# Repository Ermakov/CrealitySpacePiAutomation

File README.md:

# Creality SpacePi automation and control module
This is PCB and Arduino IDE sketch for Creality Space Pi (Plus or not) automation.

Description:
- necessary the module itself and IDC10 female-male cable
- can be inserted into any Creality SpacePi dryer (double, single, built-in Creality CFS or not)
- other functions and cables are optional (backlights, external control and power are not required for operation, but can be connected additionally)
- the cable from the SpacePi display needs to be disconnected from the dryer board and inserted into the "display" socket on the module
- an additional IDC10 cable connecting between the module "mainboard" socket and the dryer board (power is supplied from the dryer board via this cable)
- RJ45 on the module connecting to any I2C master using a regular patch cord and provides data transfer in both directions, and also serves lighting (24V led strip) inside CFS or dryer
- two pin terminal block on the module used for connecting the led strip; pad J4 on the back of the module (via diode) used for supply 24 volts to the strip directly from CFS (without connecting a patch cord with external power)

Module/sketch features:
- interception of all signals between the display/buttons and the dryer board, the module sees the readings on the display and can control the dryer buttons
- automatic switching on SpacePi after power is supplied
- automatic switching on SpacePi drying mode to the values on the display when the module sees humidity above the set point (by default 30%, switching on for 4 hours, then a break of 4 hours, and so on)
- solving the problem with the E4 error (when the dryer does not reach the expected temperature within 10 minutes) by restarting the drying mode every 9 minutes (until heating to the working temperature)
- transferring data of temperature/humidity in the dryer via I2C as HTU21D sensor protocol
- any information from the dryer display (including an error), as well as pressing any buttons using special I2C commands (see the sketch)

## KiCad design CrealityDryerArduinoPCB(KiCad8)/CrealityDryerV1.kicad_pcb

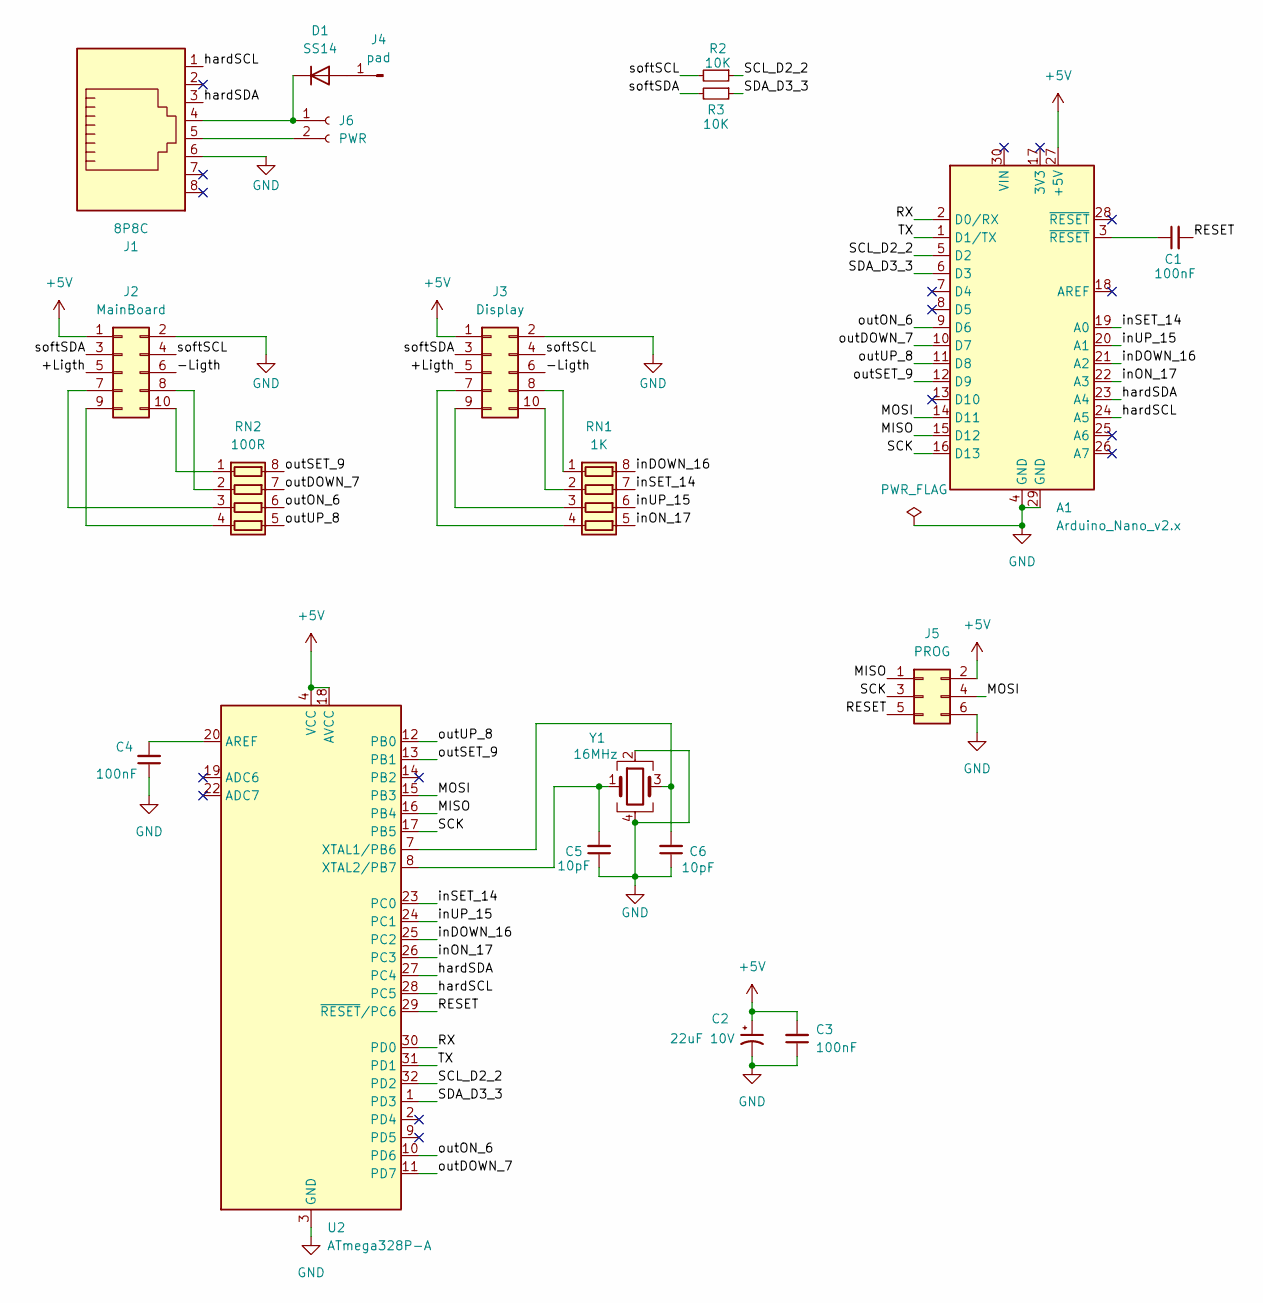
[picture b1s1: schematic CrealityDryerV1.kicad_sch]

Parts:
A1: Arduino_Nano_v2.x; Arduino_Nano
C1, C3, C4: 100nF; C_0603_1608Metric
C2: 22uF 10V; CP_EIA-3528-12_Kemet-T
C5, C6: 10pF; C_0603_1608Metric
D1: SS14; D_SMA
J1: 8P8C; RJ45_OST_PJ012-8P8CX_VerticalSensor
J2: MainBoard; IDC-Famale_2x05_P2.54mm_VerticalSilk
J3: Display; IDC-Header_2x05_P2.54mm_VerticalSilk
J4: pad; TestPoint_Pad_1.5x1.5mm
J5: PROG; PinHeader_2x03_P2.54mm_Vertical
J6: PWR; DG141R-2.54-02P
R2, R3: 10K; R_0603_1608Metric
RN1: 1K; R_Array_Convex_4x0603
RN2: 100R; R_Array_Convex_4x0603
U2: ATmega328P-A; TQFP-32_7x7mm_P0.8mm
Y1: 16MHz; Crystal_SMD_3225-4Pin_3.2x2.5mm

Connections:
+5V: A1.27 (+5V), C2.1, C3.2, J2.1, J3.1, J5.2, U2.4 (VCC), U2.6 (VCC), U2.18 (AVCC)
/+Ligth: J2.5, J3.5
/-Ligth: J2.6, J3.6
/MISO: A1.15 (D12), J5.1, U2.16 (PB4)
/MOSI: A1.14 (D11), J5.4, U2.15 (PB3)
/RESET: C1.2, J5.5, U2.29 (~RESET/PC6)
/RX: A1.2 (D0/RX), U2.30 (PD0)
/SCK: A1.16 (D13), J5.3, U2.17 (PB5)
/SCL_D2_2: A1.5 (D2), R2.1, U2.32 (PD2)
/SDA_D3_3: A1.6 (D3), R3.1, U2.1 (PD3)
/TX: A1.1 (D1/TX), U2.31 (PD1)
/hardSCL: A1.24 (A5), J1.1, U2.28 (PC5)
/hardSDA: A1.23 (A4), J1.3, U2.27 (PC4)
/inDOWN_16: A1.21 (A2), RN1.8 (R1.2), U2.25 (PC2)
/inON_17: A1.22 (A3), RN1.5 (R4.2), U2.26 (PC3)
/inSET_14: A1.19 (A0), RN1.7 (R2.2), U2.23 (PC0)
/inUP_15: A1.20 (A1), RN1.6 (R3.2), U2.24 (PC1)
/outDOWN_7: A1.10 (D7), RN2.7 (R2.2), U2.11 (PD7)
/outON_6: A1.9 (D6), RN2.6 (R3.2), U2.10 (PD6)
/outSET_9: A1.12 (D9), RN2.8 (R1.2), U2.13 (PB1)
/outUP_8: A1.11 (D8), RN2.5 (R4.2), U2.12 (PB0)
/softSCL: J2.4, J3.4, R2.2
/softSDA: J2.3, J3.3, R3.2
GND: A1.4 (GND), A1.29 (GND), C2.2, C3.1, C4.1, C5.1, C6.1, J1.6, J2.2, J3.2, J5.6, U2.3 (GND), U2.5 (GND), U2.21 (GND), Y1.2, Y1.4
unnamed: A1.3 (~RESET), C1.1
unnamed: D1.2 (A), J4.1
unnamed: D1.1 (K), J1.4, J6.1
unnamed: J2.7, RN2.3 (R3.1)
unnamed: J2.8, RN2.2 (R2.1)
unnamed: J2.9, RN2.4 (R4.1)
unnamed: J2.10, RN2.1 (R1.1)
unnamed: J3.7, RN1.4 (R4.1)
unnamed: J3.8, RN1.1 (R1.1)
unnamed: J3.9, RN1.3 (R3.1)
unnamed: J3.10, RN1.2 (R2.1)
unnamed: J1.5, J6.2
unnamed: C4.2, U2.20 (AREF)
unnamed: C6.2, U2.7 (XTAL1/PB6), Y1.3
unnamed: C5.2, U2.8 (XTAL2/PB7), Y1.1

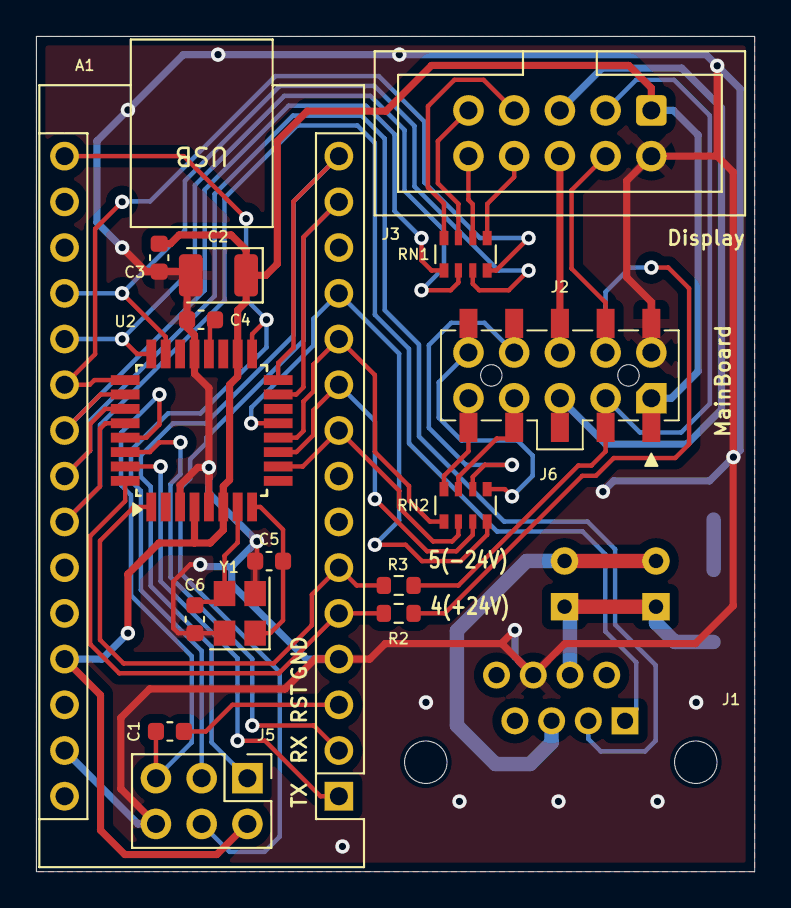
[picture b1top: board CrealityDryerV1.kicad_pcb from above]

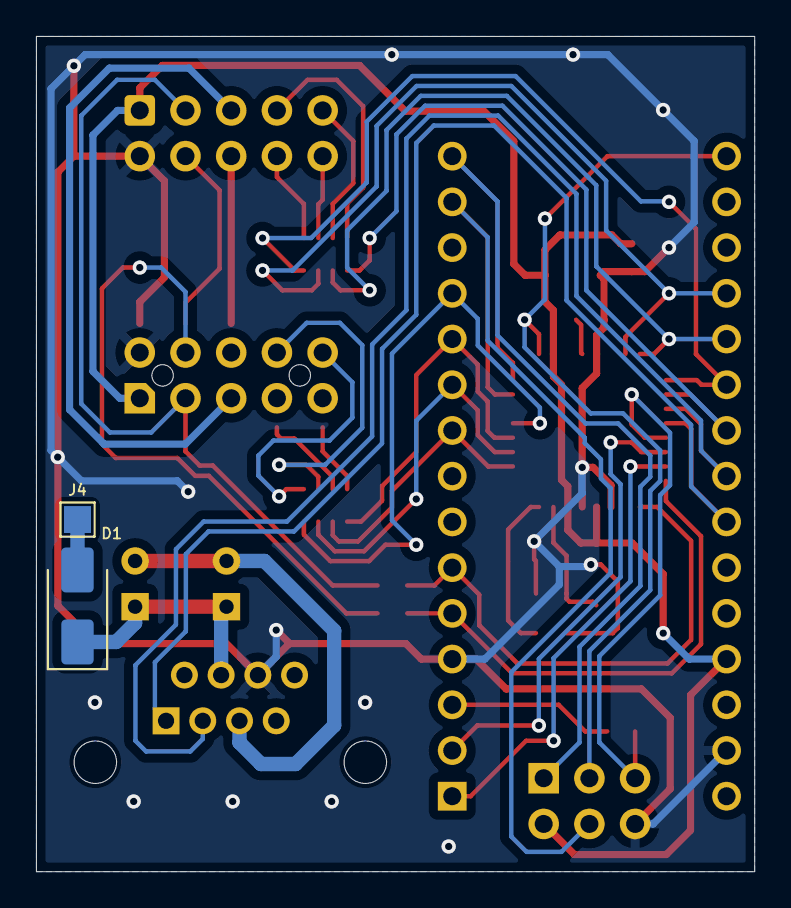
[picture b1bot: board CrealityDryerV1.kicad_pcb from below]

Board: 2 copper layers, 39.9 x 46.4 mm, 20 parts (2 on the bottom side), 39 nets.
